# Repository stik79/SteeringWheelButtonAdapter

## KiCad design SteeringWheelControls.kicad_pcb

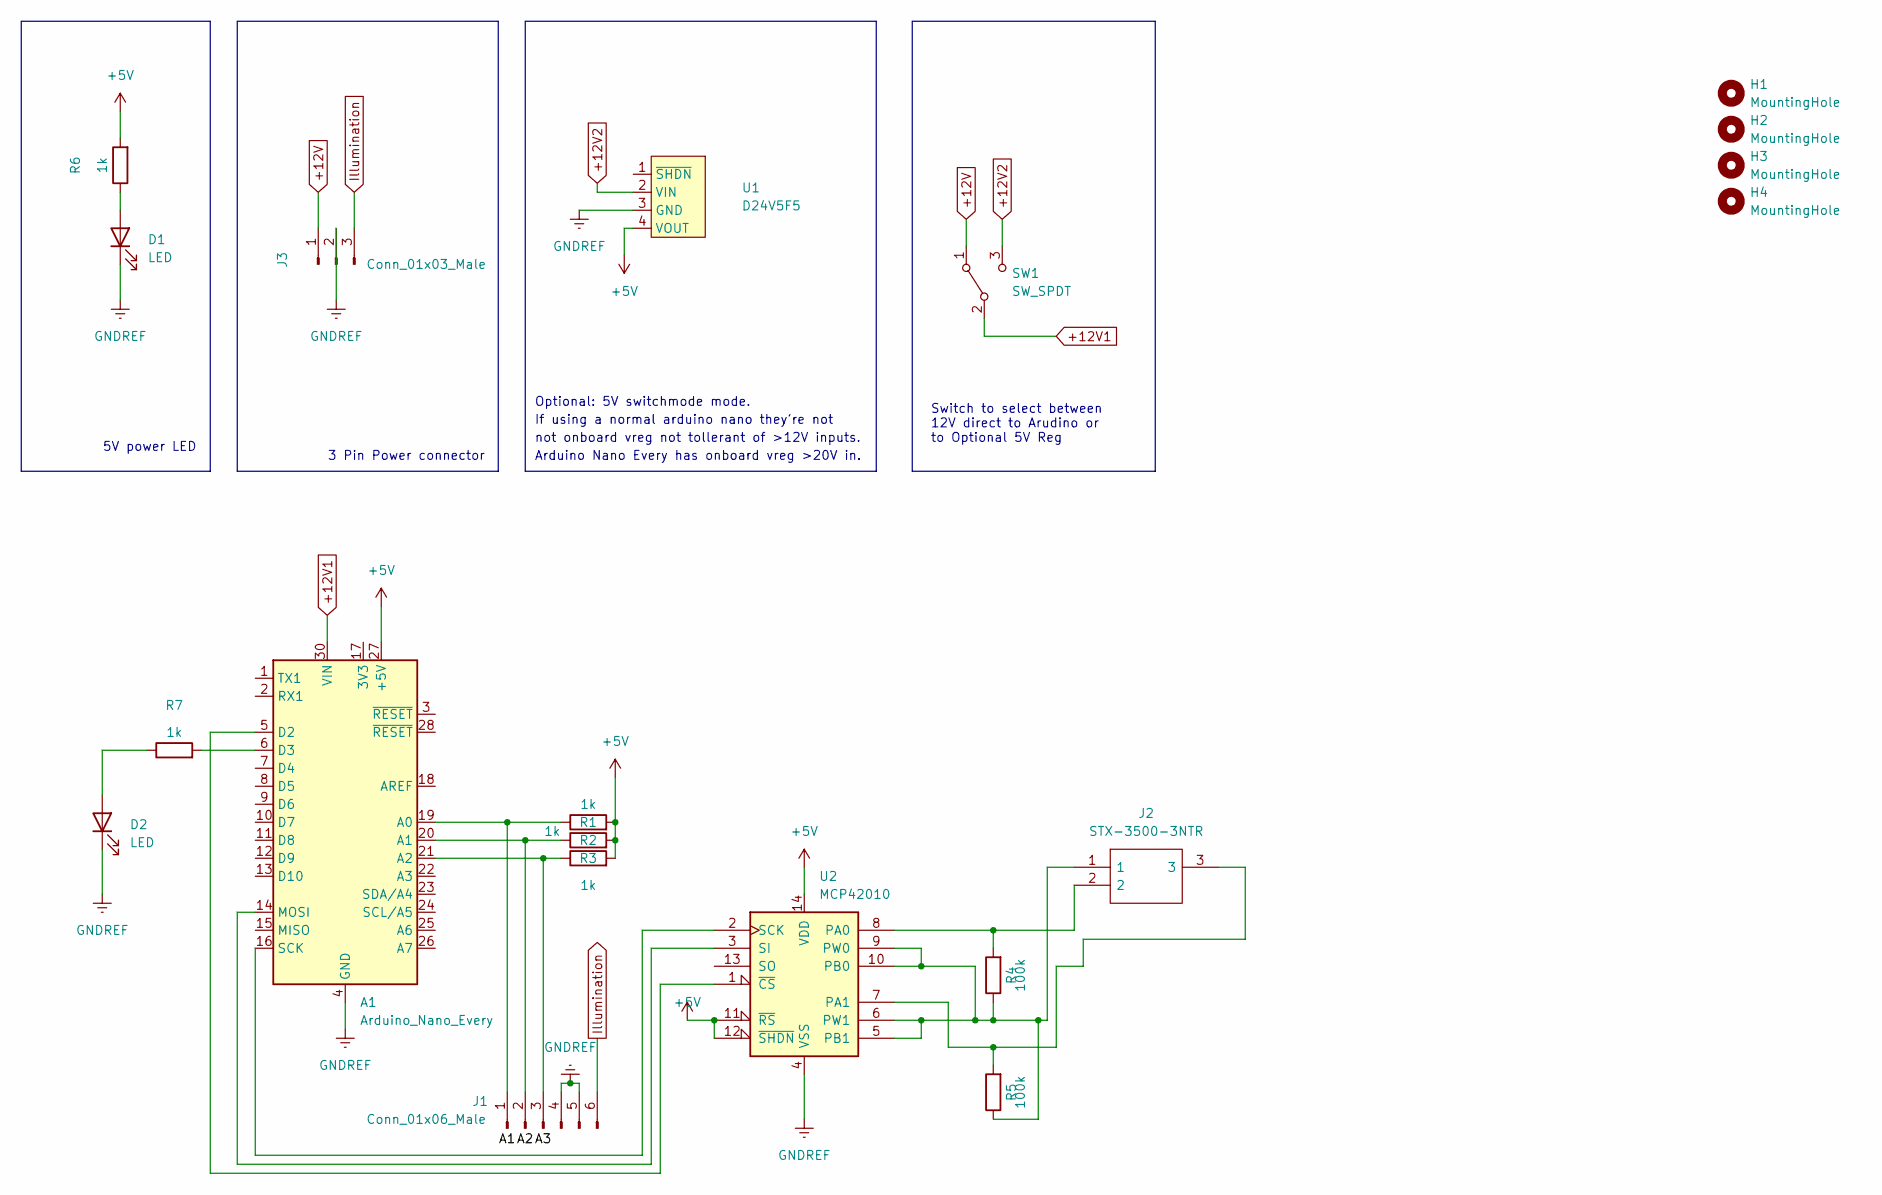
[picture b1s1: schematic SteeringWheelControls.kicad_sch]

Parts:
A1: Arduino_Nano_Every; Arduino_Nano_mat
D1, D2: LED; LED_1206_3216Metric_Pad1.42x1.75mm_HandSolder
H1, H2, H3, H4: MountingHole; MountingHole_3.2mm_M3
J1: Conn_01x06_Male; 705510005
J2: STX-3500-3NTR; STX35003NTR; Mouser Part Number 806-STX-3500-3NTR
J3: Conn_01x03_Male; 705510002
R1, R2, R3, R6, R7: 1k; R_1206_3216Metric_Pad1.30x1.75mm_HandSolder
R4, R5: 100k; R_1206_3216Metric_Pad1.30x1.75mm_HandSolder
SW1: SW_SPDT; 090320102
U1: D24V5F5
U2: MCP42010; DIP-14_W7.62mm

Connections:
+5V: A1.27 (+5V), R1.2, R2.2, R3.2, R6.2, U1.4 (VOUT), U2.11 (~RS), U2.12 (~SHDN), U2.14 (VDD)
+12V: J3.1, SW1.1 (A)
+12V1: A1.30 (VIN), SW1.2 (B)
+12V2: SW1.3 (C), U1.2 (VIN)
GNDREF: A1.4 (GND), A1.29 (GND), D1.1 (K), D2.1 (K), J1.4, J1.5, J3.2, U1.3 (GND), U2.4 (VSS)
Illumination: J1.6, J3.3
unnamed: A1.19 (A0), J1.1, R1.1
unnamed: A1.20 (A1), J1.2, R2.1
unnamed: A1.21 (A2), J1.3, R3.1
unnamed: A1.5 (D2), U2.1 (~CS)
unnamed: A1.6 (D3), R7.2
unnamed: A1.14 (MOSI), U2.3 (SI)
unnamed: A1.16 (SCK), U2.2 (SCK)
unnamed: D1.2 (A), R6.1
unnamed: D2.2 (A), R7.1
unnamed: J2.2, R4.2, U2.8 (PA0)
unnamed: J2.3, R5.2, U2.7 (PA1)
unnamed: J2.1, R4.1, R5.1, U2.5 (PB1), U2.6 (PW1), U2.9 (PW0), U2.10 (PB0)

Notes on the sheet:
Arduino Nano Every has onboard vreg >20V in.
3 Pin Power connector
Switch to select between 12V direct to Arudino or to Optional 5V Reg
5V power LED
Optional: 5V switchmode mode.
If using a normal arduino nano they're not
not onboard vreg not tollerant of >12V inputs.

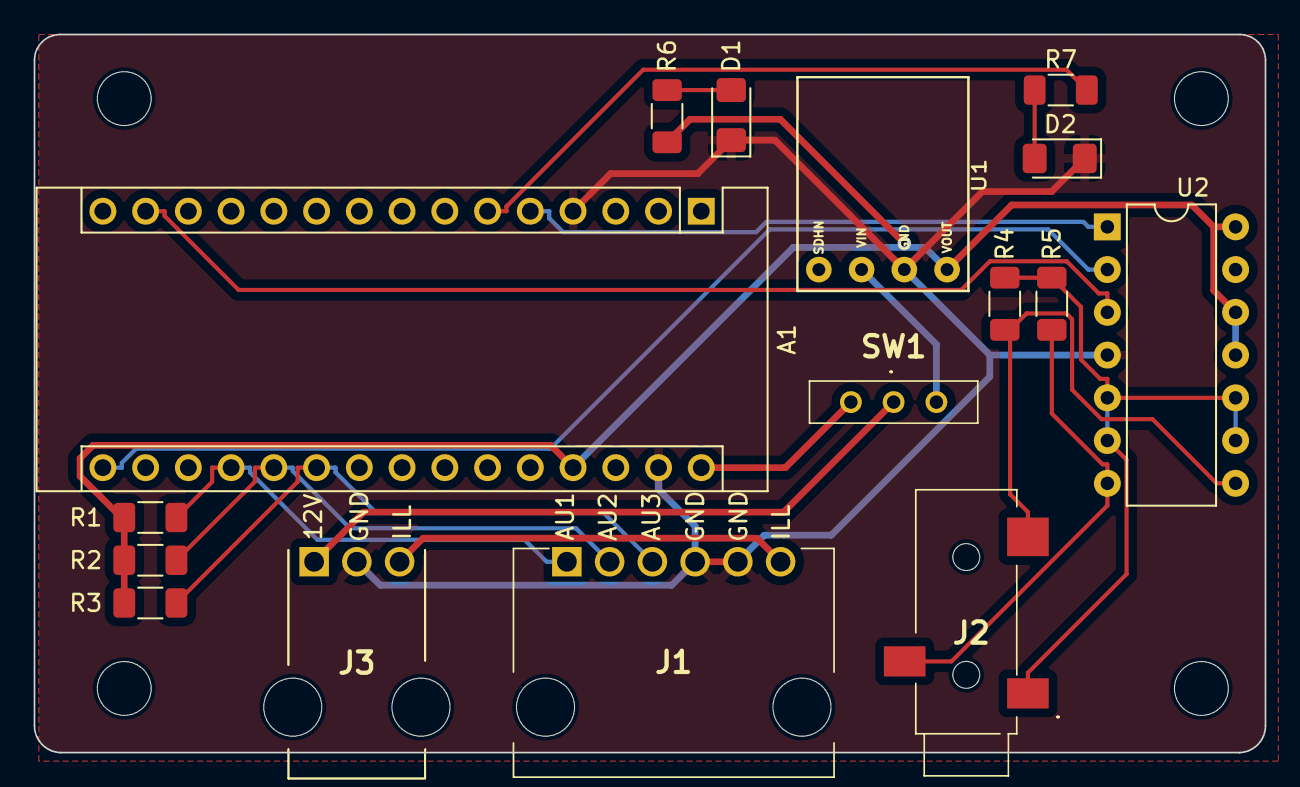
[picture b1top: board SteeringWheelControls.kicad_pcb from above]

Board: 2 copper layers, 73.2 x 42.7 mm, 20 parts (0 on the bottom side), 18 nets.

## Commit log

2023-10-18 Schematic Initial Checkin
2023-10-18 Create LICENSE
2023-10-18 Added BOM
